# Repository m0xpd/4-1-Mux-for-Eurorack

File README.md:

# A Dual Channel 4:1 Multiplexer for Eurorack

This project describes a multiplexer (similar to a "sequential switch") for electronic music applications.

The main system, implemented in a 12HP module, has two 4:1 multiplexers, each of which can switch audio or "CV" signals. The switching can be performed manually, under CV control, or synchronously with an external or internal clock. When clocked, the system can either i) follow the CV input requests (switching synchronously with the clock), ii) advance in a repetitive, finite arithmetic sequence through the inputs or iii) 'shuffle' the inputs randomly. When externally clocked, a "clock divide" feature is available and the system can clock on rising or falling edges of the external clock. The system can be set to cycle (sequentially or randomly) through the first 2, 3 or 4 of the available inputs and can be reset to input 1 on application of an external reset pulse.

The main system also features four potentiometers to generate voltages which are normalled to the 'X' channel inputs of the multiplexer, making it easy to (e.g.) generate CV sequences etc..

Note that, unlike some 'sequential switches' (such as the Doepfer A151), the system is unidirectional; it passes signals only from inputs to outputs. 

The system is based upon a conventional  4052 CMOS analog multiplexer, which is operated between -5V and +5V (to allow safe passage of bipolar signals). Signals are first attenuated (by around 10dB) by passive attenuators before entering the multiplexer and subsequently amplified to restore the signal level. This allows full-scale 'Eurorack' signals to be handled and avoids the non-linearity at the extremes of the multiplexer's transfer characteristic. The system is implemented using Surface Mount components (1206) and the multiplexer switching control is achieved by an Arduino Nano. Although the microcontroller's processing speed will never allow this system to be as fast as pure hardware multiplexers, it has been shown capable of clocking the inputs at frequencies over 2kHz using the code in the 'Controller' folder of this repository (this was with an external clock, of course - the internal clock has been programmed such that the 'rate' control delevers clock frequencies between 0.25 Hz and 13.5 Hz).

The expense of precision resistors for the input attenuators was avoided by measuring and selecting from 1% stock. It was found easy to achieve 0.1% equivalent tolerance in system gain.   

The main multiplexer module draws 25mA from the 12V supply (80% of which is for the Arduino) and 4mA from the -12V supply.

# System Expansion for Multi-Channel Operation

A 'Slave' system, also in 12HP, provides another two channels of multiplexing under the control of the main system. 

The 'X' channel of the slave unit also has potentiometers offering four voltages to its normalled inputs. 

The slave system is connected to the main system by a ribbon cable, which allows the slave multiplexer to track the switching sequence of the main controller. The slave unit requires an independent eurorack power cable. 

The slave multiplexer module draws 4mA from the 12V supply and 3mA from the -12V supply.

Multiple 'slaves' can be driven by a single main system, allowing 4, 6, 8 ... channel 4:1 mutiplexer systems to be easily constructed - I now run a 6 channel 4:1 mux in my system, using 
a main unit and two slaves...

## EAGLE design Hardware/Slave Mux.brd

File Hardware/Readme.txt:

This folder contains Eagle files defining the hardware for the master multiplexer and the slave unit.

There is also an Eagle library for the Thonk Low-profile illuminated push button, used in the design.

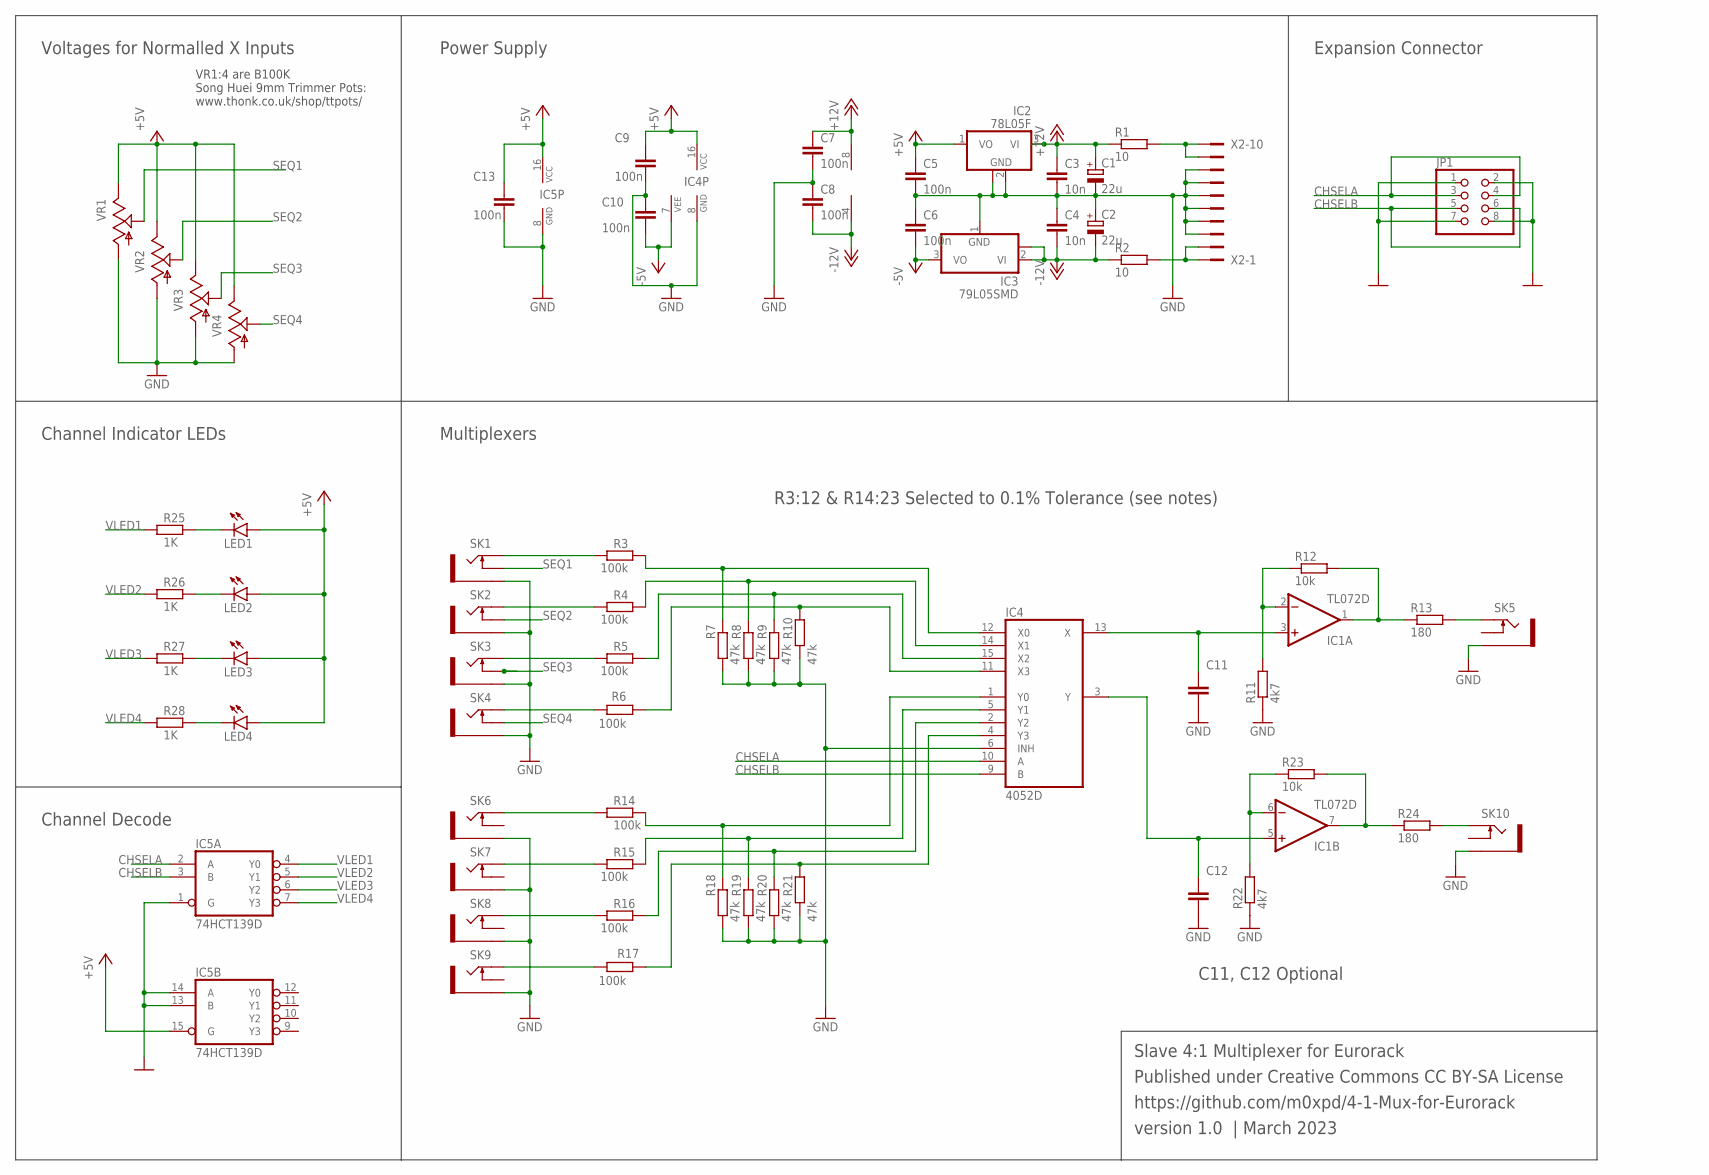
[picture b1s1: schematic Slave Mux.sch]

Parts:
C1, C2: 22u; 153CLV-0505
C3, C4: 10n; C1206
C5, C6, C7, C8, C9, C10, C13: 100n; C1206
C11, C12: C-EUC1206; C1206
IC1: TL072D; SO08
IC2: 78L05F; SOT89
IC3: 79L05SMD; SOT89
IC4: 4052D; SO16
IC5: 74HCT139D; SO16
JP1: PINHD-2X4; 2X04
LED1, LED2, LED3, LED4: LED3MM
R1, R2: 10; M1206
R3, R4, R5, R6, R14, R15, R16, R17: 100k; M1206
R7, R8, R9, R10, R18, R19, R20, R21: 47k; M1206
R11, R22: 4k7; R1206
R12, R23: 10k; R1206
R13, R24: 180; M1206
R25, R26, R27, R28: 1K; M1206
SK1, SK2, SK3, SK4, SK5, SK6, SK7, SK8, SK9, SK10: THONKICONN_JACK; WQP-PJ301M-12_JACK
VR1, VR2, VR3, VR4: 9MM_VERTICAL_POT; 9MM_SNAP-IN_POT
X2: 2510-; PAK100/2500-10

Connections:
+5V: C5.1, C9.1, C13.1, IC2.1 (VO), IC4.16 (VCC), IC5.15 (G), IC5.16 (VCC), LED1.A, LED2.A, LED3.A, LED4.A, VR1.3 (E), VR2.3 (E), VR3.3 (E), VR4.3 (E)
+12V: C1.+, C3.1, C7.1, IC1.8 (V+), IC2.3 (VI), R1.1
-5V: C6.2, C10.2, IC3.3 (VO), IC4.7 (VEE)
-12V: C2.-, C4.2, C8.2, IC1.4 (V-), IC3.2 (VI), IC3.2@1 (VI), R2.1
CHSELA: IC4.10 (A), IC5.2 (A), JP1.3, JP1.4
CHSELB: IC4.9 (B), IC5.3 (B), JP1.5, JP1.6
GND: C1.-, C2.+, C3.2, C4.1, C5.2, C6.1, C7.2, C8.1, C9.2, C10.1, C11.2, C12.2, C13.2, IC2.2 (GND), IC2.2@1 (GND), IC3.1 (GND), IC4.6 (INH), IC4.8 (GND), IC5.1 (G), IC5.8 (GND), IC5.13 (B), IC5.14 (A), JP1.1, JP1.2, JP1.7, JP1.8, R7.1, R8.1, R9.1, R10.1, R11.1, R18.1, R19.1, R20.1, R21.1, R22.1, SK1.P$3_SLEEVE (SLEEVE), SK2.P$3_SLEEVE (SLEEVE), SK3.P$3_SLEEVE (SLEEVE), SK4.P$3_SLEEVE (SLEEVE), SK5.P$3_SLEEVE (SLEEVE), SK6.P$3_SLEEVE (SLEEVE), SK7.P$3_SLEEVE (SLEEVE), SK8.P$3_SLEEVE (SLEEVE), SK9.P$3_SLEEVE (SLEEVE), SK10.P$3_SLEEVE (SLEEVE), VR1.1 (A), VR2.1 (A), VR3.1 (A), VR4.1 (A), X2.3, X2.4, X2.5, X2.6, X2.7, X2.8
unnamed: IC4.12 (X0), R3.2, R7.2
unnamed: IC4.14 (X1), R4.2, R8.2
unnamed: IC4.15 (X2), R5.2, R9.2
unnamed: C11.1, IC1.3 (+IN), IC4.13 (X)
unnamed: IC1.2 (-IN), R11.2, R12.1
unnamed: IC1.1 (OUT), R12.2, R13.1
unnamed: R3.1, SK1.P$1_TIP (TIP)
unnamed: IC4.11 (X3), R6.1, R10.2
unnamed: R4.1, SK2.P$1_TIP (TIP)
unnamed: R5.1, SK3.P$1_TIP (TIP)
unnamed: R6.2, SK4.P$1_TIP (TIP)
unnamed: LED1.K (C), R25.2
unnamed: R13.2, SK5.P$1_TIP (TIP)
unnamed: IC4.1 (Y0), R14.2, R18.2
unnamed: R1.2, X2.9, X2.10
unnamed: R2.2, X2.1, X2.2
unnamed: IC4.5 (Y1), R15.2, R19.2
unnamed: IC4.2 (Y2), R16.2, R20.2
unnamed: IC4.4 (Y3), R17.1, R21.2
unnamed: R14.1, SK6.P$1_TIP (TIP)
unnamed: R15.1, SK7.P$1_TIP (TIP)
unnamed: R16.1, SK8.P$1_TIP (TIP)
unnamed: R17.2, SK9.P$1_TIP (TIP)
unnamed: LED4.K (C), R28.2
unnamed: C12.1, IC1.5 (+IN), IC4.3 (Y)
unnamed: IC1.6 (-IN), R22.2, R23.1
unnamed: IC1.7 (OUT), R23.2, R24.1
unnamed: R24.2, SK10.P$1_TIP (TIP)
unnamed: LED2.K (C), R26.2
unnamed: LED3.K (C), R27.2
SEQ1: SK1.P$2_SWITCH (SWITCH), VR1.2 (S)
SEQ2: SK2.P$2_SWITCH (SWITCH), VR2.2 (S)
SEQ3: SK3.P$2_SWITCH (SWITCH), VR3.2 (S)
SEQ4: SK4.P$2_SWITCH (SWITCH), VR4.2 (S)
VLED1: IC5.4 (Y0), R25.1
VLED2: IC5.5 (Y1), R26.1
VLED3: IC5.6 (Y2), R27.1
VLED4: IC5.7 (Y3), R28.1

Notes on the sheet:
Slave 4:1 Multiplexer for Eurorack
Published under Creative Commons CC BY-SA License
https://github.com/m0xpd/4-1-Mux-for-Eurorack
version 1.0 | March 2023
R3:12 & R14:23 Selected to 0.1% Tolerance (see notes)
Voltages for Normalled X Inputs
Power Supply
Expansion Connector
Channel Indicator LEDs
Multiplexers
Channel Decode
C11, C12 Optional
VR1:4 are B100K Song Huei 9mm Trimmer Pots: www.thonk.co.uk/shop/ttpots/

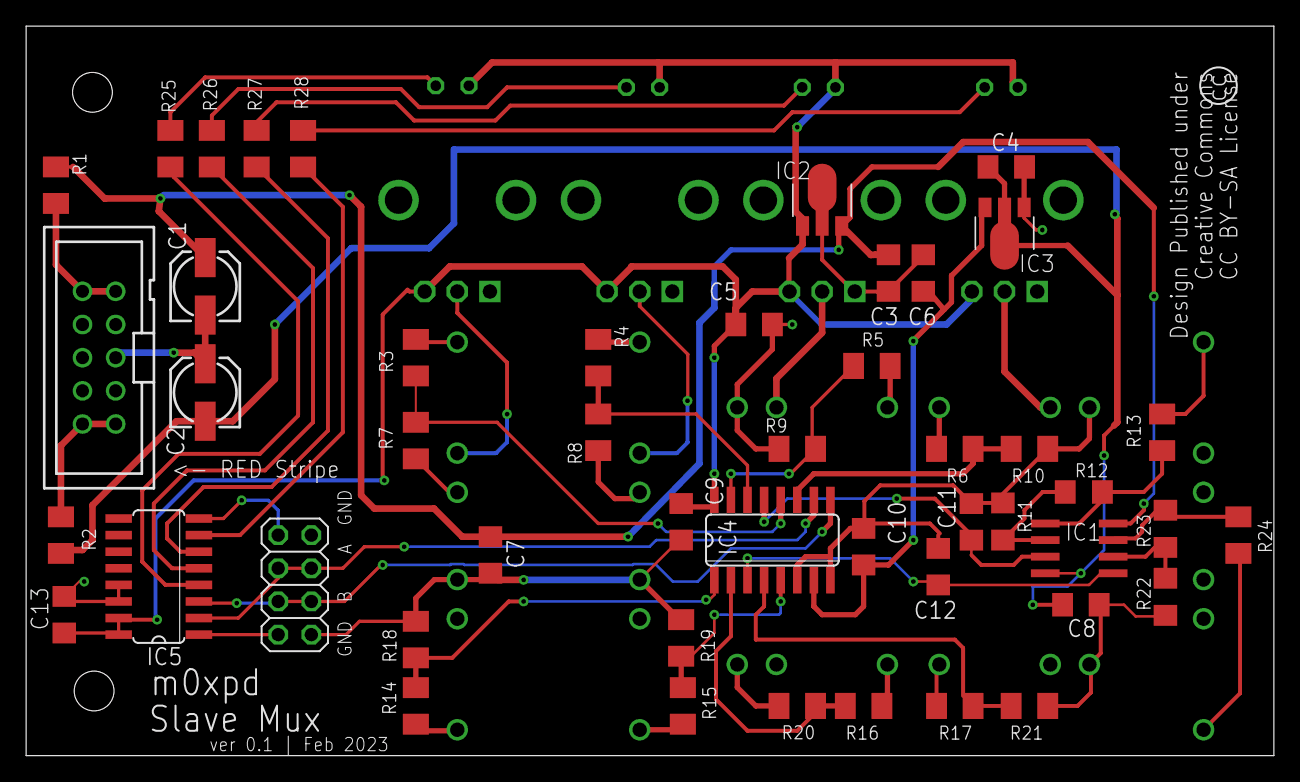
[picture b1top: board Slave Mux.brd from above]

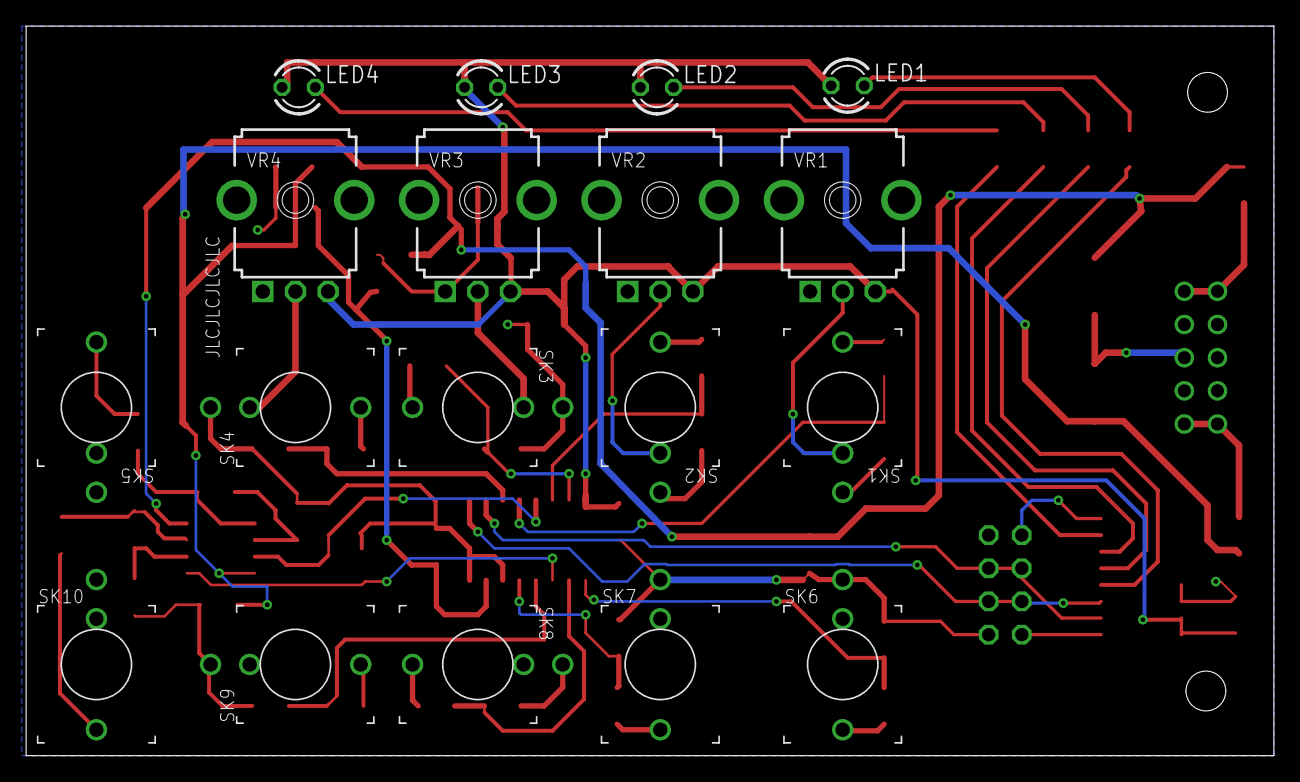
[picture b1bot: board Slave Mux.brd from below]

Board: 2 copper layers, 95.6 x 55.9 mm, 66 parts (18 on the bottom side), 45 nets.

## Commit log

2023-03-06 Rename Dual 4-1 Mux.brd to Hardware/Dual 4-1 Mux.brd
2023-03-06 Rename Dual 4-1 Mux.sch to Hardware/Dual 4-1 Mux.sch
2023-03-06 Rename Slave Mux.brd to Hardware/Slave Mux.brd
2023-03-06 Rename Slave Mux.sch to Hardware/Slave Mux.sch
2023-03-06 Rename Dual_4-1_Mux_Controller.ino to Controller/Dual_4-1_Mux_Controller.ino
2023-03-06 Rename Readme.txt to INFO.md
2023-03-06 Rename Hardware/Dual 4-1 Mux.kicad_pcb to Hardware/Mux Front Panel/Dual 4-1 Mux.kicad_pcb
2023-03-06 Rename Hardware/Dual 4-1 Mux.kicad_pro to Hardware/Mux Front Panel/Dual 4-1 Mux.kicad_pro
2023-03-06 Rename Hardware/Dual 4-1 Mux.kicad_sch to Hardware/Mux Front Panel/Dual 4-1 Mux.kicad_sch
2023-03-06 Rename Hardware/Slave Mux Front Panel.kicad_pcb to Hardware/Slave Front Panel/Slave Mux Front Panel.kicad_pcb
2023-03-06 Rename Hardware/Slave Mux Front Panel.kicad_pro to Hardware/Slave Front Panel/Slave Mux Front Panel.kicad_pro
2023-03-06 Rename Hardware/Slave Mux Front Panel.kicad_sch to Hardware/Slave Front Panel/Slave Mux Front Panel.kicad_sch
2023-04-15 Rename INFO.md to README.md

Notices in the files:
Hardware/Slave Mux.brd:
Design Published under
Creative Commons
CC BY-SA License
